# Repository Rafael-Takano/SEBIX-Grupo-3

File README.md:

# SEBIX-Grupo-3
## Descrição do Projeto
Desenvolvimento de um jogo arcade inspirado no "T-Rex Game" do Google Chrome em Arduino, realizado como projeto de treinamento de trabalho em grupo e consolidação de conceitos aprendidos no treinamento da ada. 
## Protótipo
O protótipo foi montado e testado por meio do TinkerCad, utilizando:
- 1 Arduino UNO
- 1 Buzzer 
- 1 Display de LCD 16x2
- 1 Potenciômetro de 250 kOhm
- 1 Protoboard 
- 1 Pushbutton
- 2 Resistores de 1 kOhm 

E foi montado assim como na imagem abaixo.

## Código
- #### Breve descrição do funcionamento do jogo
Inicialmente ao ligar o Arduino à uma fonte de energia o jogo fica numa tela inicial esperando o input do jogador para começar:

Em seguida, com o clique do jogador, começa o jogo e toca a melodia de inicio de game. 

O objetivo do jogador é evitar os cactos que vem em sua direção, a pontuação disposta no canto superior direito é contado com base no tempo de jogo, ao clicar no botão o dinossauro pula e o buzzer emite o som de pulo.

Ao colidir-se com um cacto o jogo termina e é exibida a tela de Game Over e toca-se a musica de fim de jogo.

Caso haja interesse, o link do código está abaixo:
- **[Código do jogo](/codigo-sebix-grupo3.ino.ino)**

## PCB
A placa de circuito impresso foi produzida no software Eagle, diferentemente do protótipo nessa placa é esperado o uso do Arduino Nano pois o design fica mais compacto.

A imagem da placa com os componentes pode ser observada abaixo.

Os fios azuis representam as conexões do lado de cima da placa e o fios vermelhos a rede do lado de baixo da placa

Caso haja o interesse na producão dessa placa do jeito como foi projetada os templates estão abaixo:
 
- [Parte de cima "Fios Azuis"](https://github.com/Rafael-Takano/SEBIX-Grupo-3/blob/main/PCB_Files/Schematic_Sebix_top.pdf)
- [Parte de baixo "Fios Vermelhos"](https://github.com/Rafael-Takano/SEBIX-Grupo-3/blob/main/PCB_Files/Schematic_Sebix_bottom.pdf)

Caso haja o interesse na modificação dessa placa: 

- [Esquema](https://github.com/Rafael-Takano/SEBIX-Grupo-3/blob/main/PCB_Files/Schematic_Sebix.sch)
- [Placa](https://github.com/Rafael-Takano/SEBIX-Grupo-3/blob/main/PCB_Files/Schematic_Sebix.brd)

## Modelagem 3D
Prototipo para acoplamento da PCB, ilustrado em diferentes vistas. 

Foram adicionados componentes para ilustrar o resultado final do projeto, suas dimensões estão de acordo com os selecionados para uso. São eles:
- Display de Cristal líquido (LCD)
- Arduino nano
- Push Button
- Buzzer 5V

Produzido no Software Fusion 360 Autodesk, e os componentes citados disponíveis em https://gallery.autodesk.com/projects/all

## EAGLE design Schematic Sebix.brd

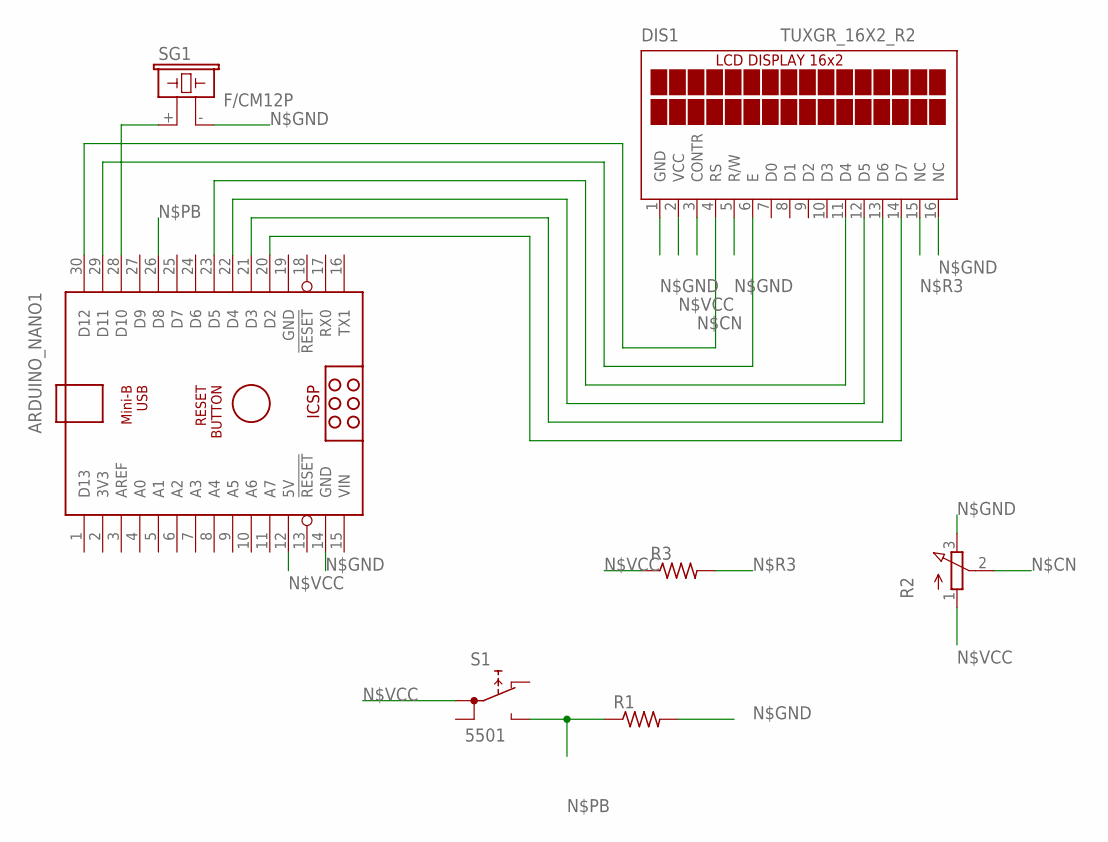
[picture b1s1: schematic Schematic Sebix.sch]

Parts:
ARDUINO_NANO1: ARDUINO_NANO
DIS1: TUXGR_16X2_R2
R1, R3: R-US_0204/5; 0204/5
R2: 3RP/1610N
S1: 5501
SG1: F/CM12P

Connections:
GND: ARDUINO_NANO1.19 (GND)
unnamed: ARDUINO_NANO1.28 (D10), SG1.+ (1)
unnamed: ARDUINO_NANO1.30 (D12), DIS1.4 (RS)
unnamed: ARDUINO_NANO1.29 (D11), DIS1.6 (E)
unnamed: ARDUINO_NANO1.23 (D5), DIS1.11 (D4)
unnamed: ARDUINO_NANO1.22 (D4), DIS1.12 (D5)
unnamed: ARDUINO_NANO1.21 (D3), DIS1.13 (D6)
unnamed: ARDUINO_NANO1.20 (D2), DIS1.14 (D7)
N$CN: DIS1.3 (CONTR), R2.2 (S)
N$GND: ARDUINO_NANO1.14 (GND), DIS1.1 (GND), DIS1.5 (R/W), DIS1.16 (NC), R1.2, R2.3 (E), SG1.- (2)
N$PB: ARDUINO_NANO1.26 (D8), R1.1, S1.NO
N$R3: DIS1.15 (NC), R3.2
N$VCC: ARDUINO_NANO1.12 (5V), DIS1.2 (VCC), R2.1 (A), R3.1, S1.1A
VIN: ARDUINO_NANO1.15 (VIN)

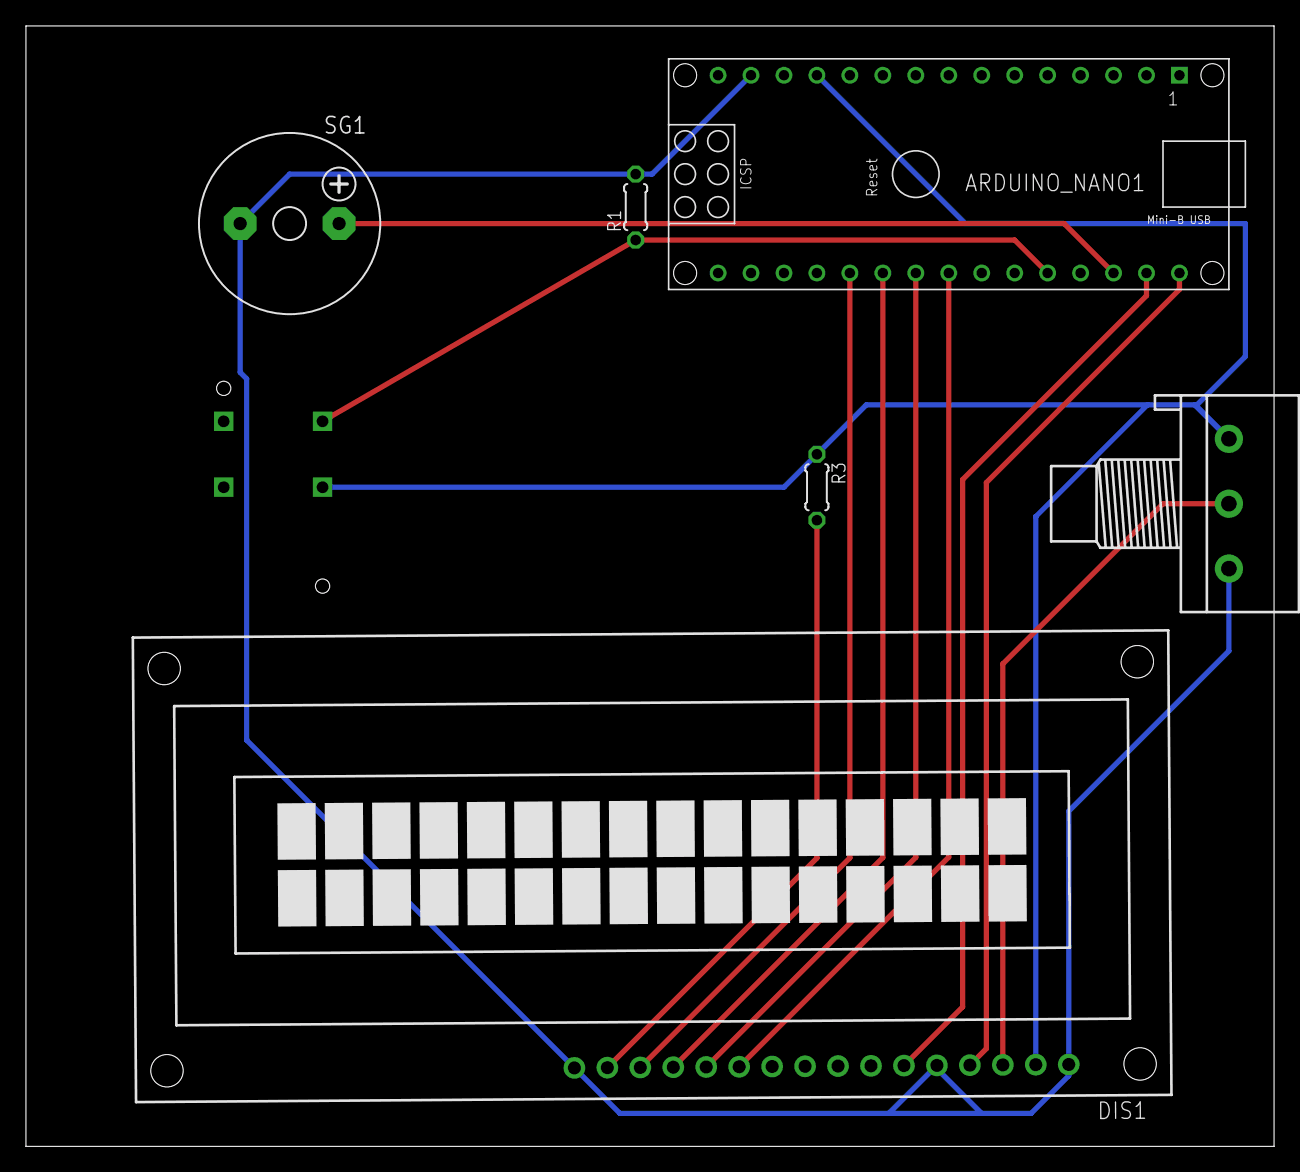
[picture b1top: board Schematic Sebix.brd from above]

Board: 2 copper layers, 96.2 x 86.3 mm, 7 parts (1 on the bottom side), 12 nets.

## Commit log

2021-03-14 Adicionei os arquivos relacionados à PCB
2021-03-14 Reorganização e melhor descrição do projeto
2021-03-14 MarkDown é mais dificil que C, change my mind
2021-03-14 mudança de nomes pro readme funcionar
2021-06-07 Adição do modelo 3D
